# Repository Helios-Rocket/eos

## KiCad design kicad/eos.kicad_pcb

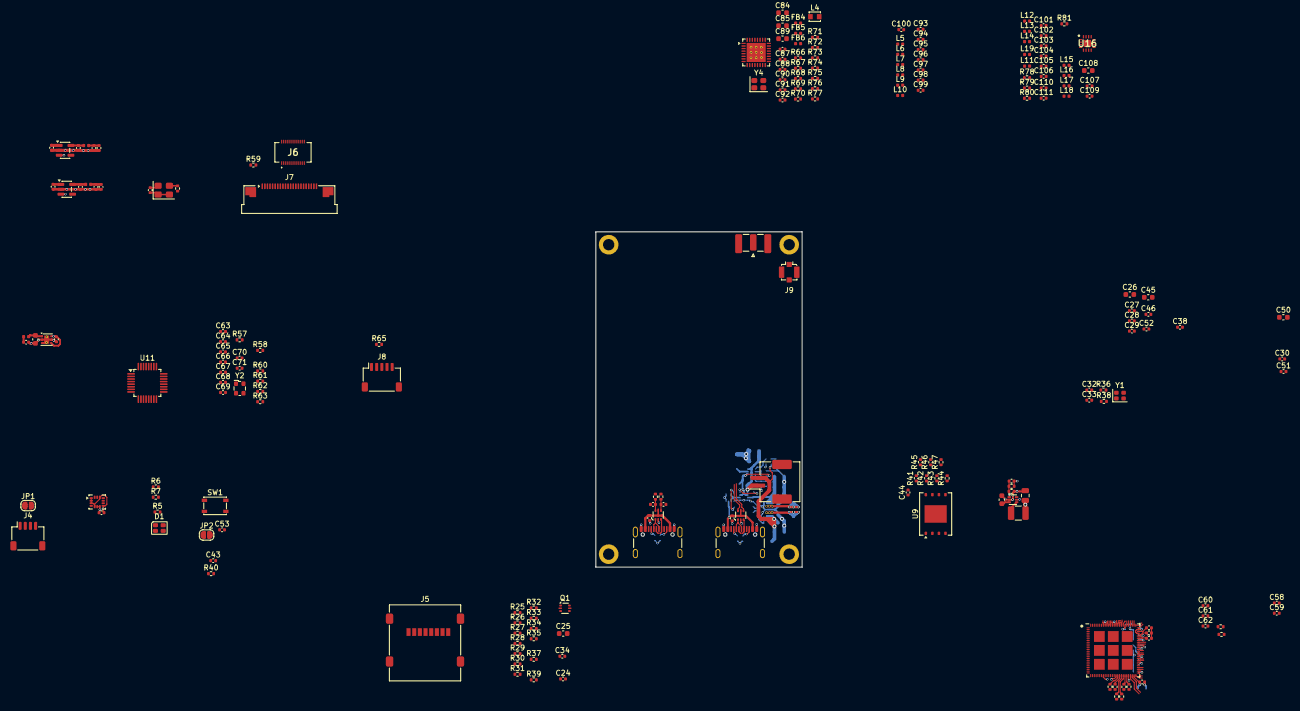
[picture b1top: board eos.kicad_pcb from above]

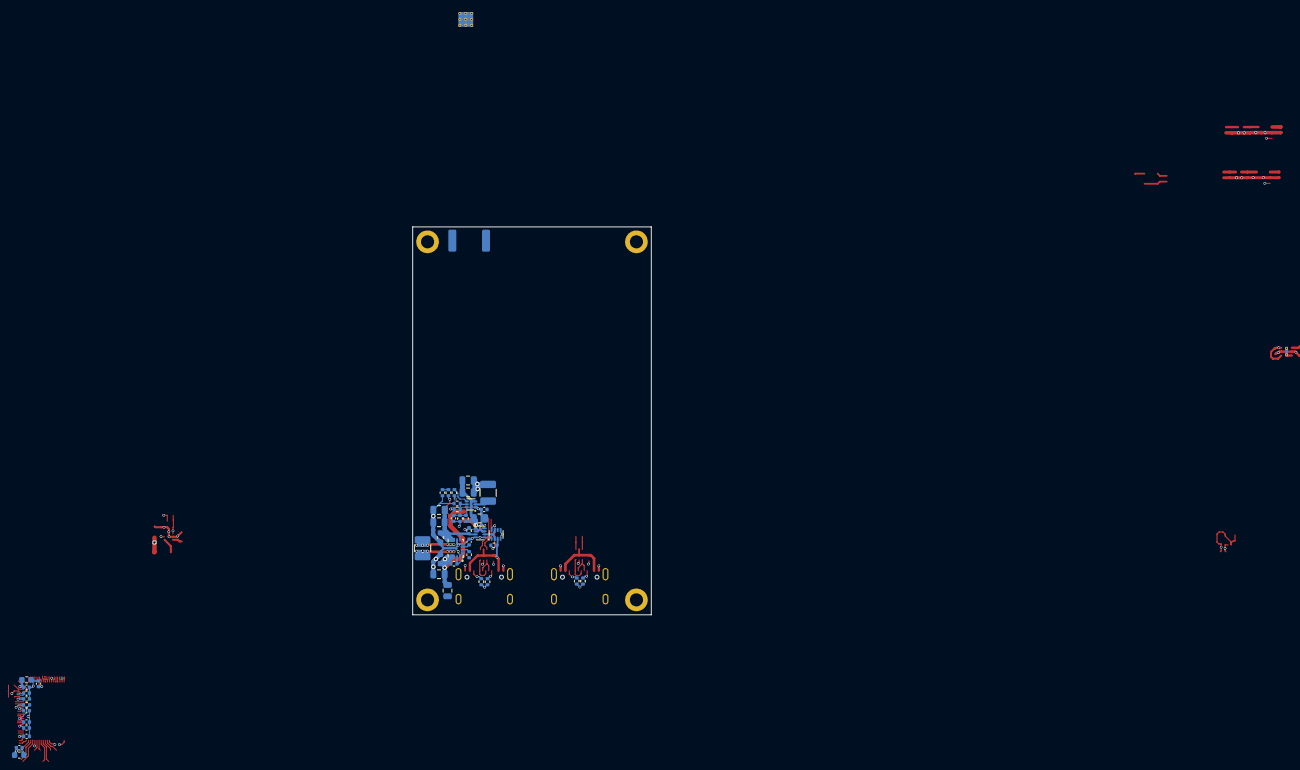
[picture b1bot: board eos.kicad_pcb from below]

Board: 4 copper layers, 40.0 x 65.0 mm, 251 parts (45 on the bottom side), 196 nets.

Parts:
C1, C11, C39, C40, C41, C42, C43, C47, C58, C60, C67, C68, C69, C72, C73, C75, C76, C78, C81, C83, C86, C87: 1u; C_0402_1005Metric
C2, C5, C25, C26, C35, C45, C50, C82: 10u; C_0603_1608Metric
C3, C4: 10u; C_0805_2012Metric
C6, C7, C17, C18, C19, C23: 22u; C_0805_2012Metric
C9, C14, C20, C24, C27, C28, C29, C30, C31, C36, C37, C38, C44, C46, C48, C49, C51, C52, C54, C57, C59, C62, C63, C64, C65, C66, C70, C71, C74, C77, C79, C88: 0.1u; C_0402_1005Metric
C12, C13, C34, C110: TBD; C_0402_1005Metric
C15: 10p; C_0402_1005Metric
C21, C95: 22p; C_0402_1005Metric
C22, C55, C89: 4.7u; C_0603_1608Metric
C32, C33: 16p; C_0402_1005Metric
C53, C56, C61, C80, C91: 10n; C_0402_1005Metric
C84, C85, C108: 2.2u; C_0603_1608Metric
C90: 1n; C_0402_1005Metric
C92: 2200p; C_0402_1005Metric
C93: 2.2p; C_0402_1005Metric
C94, C111: 18p; C_0402_1005Metric
C96, C97: 1.8p; C_0402_1005Metric
C98: 3.9p; C_0402_1005Metric
C99: 7.5p; C_0402_1005Metric
C100, C106: 47p; C_0402_1005Metric
C101: 6.8p; C_0402_1005Metric
C102: 1.1p; C_0402_1005Metric
C103: 2.0p; C_0402_1005Metric
C104: 1.2p; C_0402_1005Metric
C105: 2.7p; C_0402_1005Metric
C107, C109: 100p; C_0402_1005Metric
D1: LED_RGBA; LED_Cree-PLCC4_2x2mm_CW
FB1, FB2, FB3, FB4, FB5, FB6: BLM15BB470SN1D; L_0402_1005Metric
H1, H2, H3, H4: MountingHole_Pad; MountingHole_2.2mm_M2_DIN965_Pad
J1: Debug; USB_C_Receptacle_GCT_USB4105-xx-A_16P_TopMnt_Horizontal
J2: Video; USB_C_Receptacle_GCT_USB4105-xx-A_16P_TopMnt_Horizontal
J3: Power In; JST_ZE_SM02B-ZESS-TB_1x02-1MP_P1.50mm_Horizontal
J4: Comms; JST_SH_SM04B-SRSS-TB_1x04-1MP_P1.00mm_Horizontal
J5: Micro_SD_Card; microSD_HC_Molex_47219-2001
J6: Sensor; DF30FC24DS04V81
J7: COTS; Amphenol_F32Q-1A7x1-11022_1x22-1MP_P0.5mm_Horizontal
J8: Split 4; JST_SH_SM05B-SRSS-TB_1x05-1MP_P1.00mm_Horizontal
J9: 915M; U.FL_Molex_MCRF_73412-0110_Vertical
J10: 2.4G; SMA_Samtec_SMA-J-P-H-ST-EM1_EdgeMount
JP1: SolderJumper_2_Open; SolderJumper-2_P1.3mm_Open_RoundedPad1.0x1.5mm
JP2: Boot; SolderJumper-2_P1.3mm_Open_RoundedPad1.0x1.5mm
L1: 1.5u; L_1210_3225Metric
L2: 3.3u; L_1210_3225Metric
L3: 2.2u; L_1210_3225Metric
L4: 2.2u; L_Murata_LQH2MCNxxxx02_2.0x1.6mm
L5: 24n; L_0402_1005Metric
L6: 7.5n; L_0402_1005Metric
L7: 3.9n; L_0402_1005Metric
L8: 4.7n; L_0402_1005Metric
L9: 22n; L_0402_1005Metric
L10: 12n; L_0402_1005Metric
L11, L17: 1.1n; L_0402_1005Metric
L12: 1.6n; L_0402_1005Metric
L13: 1.5n; L_0402_1005Metric
L14: 18n; L_0402_1005Metric
L15: 0.9nH; L_0402_1005Metric
L16: 2.7n; L_0402_1005Metric
L18: 1.4n; L_0402_1005Metric
L19: 2.4n; L_0402_1005Metric
Q1: Q_Dual_NMOS_PMOS_S1G1D2S2G2D1; SOT-666
R1, R4, R12, R13: 5.1k; R_0402_1005Metric
R2, R10, R11, R19, R20, R25, R40, R41, R48, R60, R63, R65: 10k; R_0402_1005Metric
R3, R22: 100k; R_0402_1005Metric
R5, R6, R7: 330R; R_0402_1005Metric
R14, R15: 22R; R_0402_1005Metric
R16: 76.8k; R_0402_1005Metric
R17: 45.3k; R_0402_1005Metric
R18: 30k; R_0402_1005Metric
R21: 340k; R_0402_1005Metric
R23, R24: 499k; R_0402_1005Metric
R26, R27, R28, R29, R30, R31: 51k; R_0402_1005Metric
R32, R33, R34, R35, R36, R37, R38, R39, R42, R43, R44, R45, R46, R47, R49, R50, R51, R52, R53, R54, R64, R78: 0R; R_0402_1005Metric
R55, R56: 4.02k; R_0402_1005Metric
R57, R58: 37R4; R_0402_1005Metric
R59: 1k; R_0402_1005Metric
R61, R62: 2.2k; R_0402_1005Metric
R66, R69, R70, R71, R76, R77: 470R; R_0402_1005Metric
R67, R68, R72, R73, R74, R75: 220R; R_0402_1005Metric
R79, R80: TBD; R_0402_1005Metric
R81: 2k; R_0402_1005Metric
SW1: Reset; SW_SPST_PTS810
U1: TPS63071; VREG_TPS630701RNMR
U2, U5: USBLC6-2P6; SOT-666
U3, U4: LM66200; SOT-583-8
U6: TPS56425x; SOT-563
U7: LSM6DSV32X; LGA-14_3x2.5mm_P0.5mm_LayoutBorder3x4y
U8: TLV62569DRL; SOT-563
U9: GD25Q256EY; WSON-8-1EP_8x6mm_P1.27mm_EP3.4x4.3mm
U10: ESP32-P4
U11: TVP5150AM1; TQFP-32_5x5mm_P0.5mm
U12: TLV73328PDBV; SOT-23-5
U13: TLV73315PDBV; SOT-23-5
U14: TPS7A26; WSON-6-1EP_2x2mm_P0.65mm_EP1x1.6mm_ThermalVias
U15: LR2021; QFN-32-1EP_5x5mm_P0.5mm_EP3.7x3.7mm_ThermalVias
U16: SKY85329-11; QFN50P250X250X45-17N-D
Y1: 40MHz; Crystal_SMD_2016-4Pin_2.0x1.6mm
Y2: 14.31818MHz; Oscillator_SMD_ECS_2520MV-xxx-xx-4Pin_2.5x2.0mm
Y3: ECS-TXO-32CSMV; Crystal_SMD_3225-4Pin_3.2x2.5mm
Y4: ATX-12-F; Crystal_SMD_2520-4Pin_2.5x2.0mm

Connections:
5V_PG: R3.2, U1.2 (PG), U10.1 (GPIO1)
+1V5: C78.1, C79.1, FB2.2, J6.20
+1V8: C66.1, C82.1, FB3.1, U11.20 (DVDD), U14.1 (OUT)
+2V8: C73.1, C80.1, FB1.1, J6.19, U12.5 (OUT), Y3.4 (VDD)
+3.3V: C15.1, C18.1, C19.1, C20.1, C22.1, C26.1, C27.1, C28.1, C29.1, C35.1, C36.1, C38.1, C45.1, C46.1, C49.1, C52.1, C55.1, C56.1, C57.1, C65.1, C72.1, C76.1, C81.1, D1.4 (A), FB6.2, J7.22, JP1.2 (B), L2.2, Q1.4 (S), R17.1, R19.1, R40.1, R48.2, R60.1, R61.1, R62.1, R63.1, U7.1 (SDO/SA0), U7.2 (SDX), U7.3 (SCX), U7.5 (VDDIO), U7.8 (VDD), U7.12 (CS), U8.3 (VIN), U10.9 (VDD_LP), U10.21 (VDD_IO_0), U10.51 (VDD_USBPHY), U10.62 (VDD_IO_4), U10.75 (VDD_LDO), U10.77 (VDD_DCDCC), U10.96 (VDD_IO_6), U10.101 (VDD_ANA), U10.102 (VDD_BAT), U11.10 (IO_DVDD), U12.1 (IN), U13.1 (IN), U14.4 (EN), U14.6 (IN)
+5V: C14.1, C17.1, C107.2, C108.2, J8.1, L15.1, R16.1, U3.2 (VOUT), U3.7 (VOUT), U6.1 (VIN), U16.16 (VCC1)
+5VP: C2.1, C6.1, C7.1, R3.1, R10.1, U1.5 (FB), U1.7 (VOUT), U3.3 (VIN1)
+BATT: C3.1, C4.1, C5.1, J3.2, R2.1, R21.1, U1.12 (VIN)
/cameras/+2V8F: C74.1, C75.1, FB1.2, J6.18
/cameras/MCLK: J6.14, R64.2
/cameras/NTSC_IN: J8.2, R57.1
/eos/3.3PG: R19.2, U6.4 (PG)
/mcu/BOOT_MODE: JP2.2 (B), U10.66 (GPIO35)
/mcu/EN_DCDC: U8.5 (EN), U10.79 (EN_DCDC)
/mcu/FB_DCDC: C21.2, R23.2, R24.1, U8.1 (FB), U10.78 (FB_DCDC)
/mcu/FLASH_CLK: R43.2, U10.32 (FLASH_CK)
/mcu/FLASH_DI: R44.2, U10.33 (FLASH_D)
/mcu/FLASH_DO: R45.2, U10.28 (FLASH_Q)
/mcu/FLASH_HOLD: R47.2, U10.31 (FLASH_HOLD)
/mcu/FLASH_~CS: R42.2, U10.27 (FLASH_CS)
/mcu/FLASH_~WP: R46.2, U10.29 (FLASH_WP)
/mcu/SD_CLK: C34.1, R29.2, R35.2, U10.84 (GPIO43)
/mcu/SD_CMD: R28.2, R34.2, U10.86 (GPIO44)
/mcu/SD_D0: R30.2, R37.2, U10.80 (GPIO39)
/mcu/SD_D1: R31.2, R39.2, U10.81 (GPIO40)
/mcu/SD_D2: R26.2, R32.2, U10.82 (GPIO41)
/mcu/SD_D3: R27.2, R33.2, U10.83 (GPIO42)
/mcu/SD_RST: Q1.5 (G), R25.1, U10.5 (GPIO5)
/mcu/~ESP_EN: C43.1, C53.1, R40.2, SW1.2, U10.103 (CHIP_PU)
/radio/RX_EN: R67.2, U16.1 (RXEN)
/radio/TX_EN: R68.2, U16.2 (TXEN)
/radio/VR_PA: C90.1, C100.1, C106.1, L10.2, L14.2, U15.1 (VR_PA)
BATT_ADC: R21.2, R22.1, U10.98 (ADC2_CHANNEL5)
CSI_CLK+: J6.8, J7.9, R51.2
CSI_CLK-: J6.7, J7.8, R52.2
CSI_D0+: J6.9, J7.3, R50.2
CSI_D0-: J6.10, J7.2, R49.2
CSI_D1+: J6.5, J7.6, R54.2
CSI_D1-: J6.6, J7.5, R53.2
EXT_SCL: J4.4, U10.56 (GPIO27/USB1P1_P1)
EXT_SDA: J4.3, U10.55 (GPIO26/USB1P1_N1)
FID: U10.2 (GPIO2), U11.23 (FID)
GND: C1.2, C2.2, C3.2, C4.2, C5.2, C6.2, C7.2, C9.2, C11.2, C12.1, C13.2, C14.2, C17.2, C18.2, C19.2, C20.2, C22.2, C23.2, C24.2, C25.2, C26.2, C27.2, C28.2, C29.2, C30.2, C31.2, C32.1, C33.1, C34.2, C35.2, C36.2, C37.2, C38.2, C39.2, C40.2, C41.2, C42.2, C43.2, C44.2, C45.2, C46.2, C47.2, C48.2, C49.2, C50.2, C51.2, C52.2, C53.2, C54.2, C55.2, C56.2, C57.2, C58.2, C59.2, C60.2, C61.2, C62.2, C63.2, C64.2, C65.2, C66.2, C68.2, C69.2, C71.2, C72.2, C73.2, C74.2, C75.2, C76.2, C77.2, C78.2, C79.2, C80.2, C81.2, C82.2, C83.2, C84.2, C85.2, C86.2, C87.2, C88.2, C89.2, C90.2, C91.2, C93.2, C97.2, C98.2, C99.2, C100.2, C103.2, C104.2, C105.2, C106.2, C107.1, C108.1, C110.2, H1.1 (1_1), H2.1 (1_1), H3.1 (1_1), H4.1 (1_1), J1.A1 (GND), J1.A12 (GND), J1.B1 (GND), J1.B12 (GND), J2.A1 (GND), J2.A12 (GND), J2.B1 (GND), J2.B12 (GND), J3.1, J4.1, J5.6 (VSS), J6.13, J6.15, J6.17, J7.1, J7.4, J7.7, J7.10, J7.13, J7.16, J7.19, J9.2 (Ext), J10.2 (Ext), JP2.1 (A), L9.2, L17.1, Q1.1 (S), R1.2, R4.2, R12.2, R13.2, R18.2, R20.2, R22.2, R24.2, R25.2, R55.2, R56.2, R58.1, R59.1, R65.2, R79.2, R80.2, R81.2, SW1.1, U1.4 (GND), U1.6 (FB2), U1.10 (GND), U1.15 (VSEL), U2.2 (GND), U3.1 (GND), U3.4 (~ON), U3.5 (GND), U4.1 (GND), U4.4 (~ON), U4.5 (GND), U5.2 (GND), U6.3 (GND), U7.6 (GND), U7.7 (GND), U8.2 (GND), U9.4 (VSS), U9.9 (PAD), U10.105 (GND), U11.3 (PLL_AGND), U11.7 (AGND), U11.19 (DGND), U11.31 (CH_AGND), U12.2 (GND), U13.2 (GND), U14.2 (GND), U14.3 (PG), U14.5 (GND), U14.7 (GND), U15.15 (GND_DCC), U15.30 (GND), U15.33 (GND), U16.6 (GND), U16.9 (GND), U16.11 (GND), U16.13 (GND), U16.15 (GND), U16.17 (GND), Y1.2 (G), Y1.4 (G), Y2.2 (GND), Y3.1 (GND), Y3.2 (GND), Y4.1 (GND), Y4.2 (GND)
HSYNC: U10.4 (GPIO4), U11.25 (HSYNC)
IMU_INT1: U7.4 (INT1), U10.22 (GPIO20/ADC1_CHANNEL4)
IO0_PowerEN: J7.17, U10.63 (GPIO32), U12.3 (EN), U13.3 (EN)
LED_BLUE: R7.2, U10.20 (GPIO19/ADC1_CHANNEL3)
LED_GREEN: R6.2, U10.19 (GPIO18/ADC1_CHANNEL2)
LED_RED: R5.2, U10.18 (GPIO17/ADC1_CHANNEL1)
LR_BUSY: R76.2, U10.6 (GPIO6)
LR_IRQ1: R66.2, U10.13 (GPIO12)
LR_IRQ2: R69.2, U10.14 (GPIO13)
LR_IRQ3: R70.2, U10.15 (GPIO14)
LR_IRQ4: R71.2, U10.16 (GPIO15)
LR_MISO: R72.2, U10.11 (GPIO10)
LR_MOSI: R73.2, U10.8 (GPIO8)
LR_SCK: R74.2, U10.10 (GPIO9)
LR_~CS: R75.2, U10.7 (GPIO7)
LR_~RESET: R77.2, U10.12 (GPIO11)
MIPI_I2C_SCL: J6.11, J7.20, U10.61 (GPIO31)
MIPI_I2C_SDA: J6.12, J7.21, U10.60 (GPIO30)
unnamed: C12.2, R14.1, U5.6 (I/O1)
unnamed: C13.1, R15.1, U5.4 (I/O2)
unnamed: C32.2, R36.1, Y1.3
unnamed: C33.2, R38.1, Y1.1
unnamed: C70.1, R57.2, R58.2
unnamed: C93.1, C94.2, L5.1
unnamed: C95.1, C96.1, C99.1, L7.2
unnamed: C95.2, L8.1
unnamed: C96.2, C98.1, L6.2, L7.1
unnamed: C101.1, C102.1, C105.1, L12.2
unnamed: C101.2, L13.1
unnamed: C102.2, C104.1, L11.2, L12.1
unnamed: C103.1, L11.1, R78.2, R80.1
unnamed: C109.1, L17.2
unnamed: C110.1, C111.2, L19.1
unnamed: D1.3 (BK), R7.1
unnamed: D1.2 (GK), R6.1
unnamed: D1.1 (RK), R5.1
unnamed: J1.A5 (CC1), R1.1
unnamed: J1.B5 (CC2), R4.1
unnamed: J1.A6 (D+), J1.B6 (D+), U2.3 (I/O2)
unnamed: J1.A7 (D-), J1.B7 (D-), U2.1 (I/O1)
unnamed: J2.A5 (CC1), R12.1
unnamed: J2.B5 (CC2), R13.1
unnamed: J2.A6 (D+), J2.B6 (D+), U5.3 (I/O2)
unnamed: J2.A7 (D-), J2.B7 (D-), U5.1 (I/O1)
unnamed: J4.2, JP1.1 (A)
unnamed: J5.5 (CLK), R35.1
unnamed: J5.3 (CMD), R34.1
unnamed: J5.7 (DAT0), R37.1
unnamed: J5.8 (DAT1), R39.1
unnamed: J5.1 (DAT2), R32.1
unnamed: J5.2 (DAT3/CD), R33.1
unnamed: C24.1, C25.1, J5.4 (VDD), Q1.3 (D)
unnamed: J6.24, R59.2
unnamed: J8.5, Q1.6 (D)
unnamed: C94.1, C97.1, J9.1 (In), L6.1, L9.1
unnamed: C109.2, J10.1 (In), L16.1
unnamed: L5.2, U15.27 (RFO_LF), U15.28 (RFO_LF)
unnamed: R2.2, U1.1 (PS/SYNC), U1.14 (EN)
unnamed: L1.1, U1.11 (L1)
unnamed: L1.2, U1.9 (L2)
unnamed: C9.1, U1.3 (VAUX)
unnamed: R11.2, U4.8 (ST)
unnamed: R16.2, R18.1, U6.5 (EN)
unnamed: C15.2, R17.2, R20.1, U6.6 (FB)
unnamed: L2.1, U6.2 (SW)
unnamed: L3.1, U8.4 (SW)
unnamed: R43.1, U9.6 (SCLK)
unnamed: R44.1, U9.5 (SI/IO0)
unnamed: R45.1, U9.2 (SO/IO1)
unnamed: R41.2, R42.1, U9.1 (~CS)
unnamed: R47.1, U9.7 (~HOLD/~RESET/IO3)
unnamed: R46.1, U9.3 (~WP/IO2)
unnamed: R52.1, U10.45 (CSI_CLKN)
unnamed: R51.1, U10.44 (CSI_CLKP)
unnamed: R49.1, U10.42 (CSI_DATAN0)
unnamed: R53.1, U10.46 (CSI_DATAN1)
unnamed: R50.1, U10.43 (CSI_DATAP0)
unnamed: R54.1, U10.47 (CSI_DATAP1)
unnamed: R56.1, U10.48 (CSI_REXT)
unnamed: R55.1, U10.34 (DSI_REXT)
unnamed: R48.1, U10.68 (GPIO36)
unnamed: R36.2, U10.99 (XTAL_N)
unnamed: R38.2, U10.100 (XTAL_P)
unnamed: C70.2, U11.1 (AIP1A)
unnamed: C71.1, U11.2 (AIP1B)
unnamed: C67.2, C69.1, U11.30 (REFM)
unnamed: C67.1, C68.1, U11.29 (REFP)
unnamed: U11.5 (OSC), Y2.3 (OUT)
unnamed: R63.2, U11.28 (~PDN)
unnamed: C77.1, FB2.1, U13.5 (OUT)
unnamed: R76.1, U15.25 (BUSY)
unnamed: R71.1, U15.18 (DIO6)
unnamed: R70.1, U15.11 (DIO7)
unnamed: R69.1, U15.10 (DIO8)
unnamed: R68.1, U15.9 (DIO9)
unnamed: R67.1, U15.8 (DIO10)
unnamed: R66.1, U15.7 (DIO11)
unnamed: L4.2, U15.16 (LXA)
unnamed: L4.1, U15.14 (LXB)
unnamed: R72.1, U15.21 (MISO)
unnamed: R73.1, U15.22 (MOSI)
unnamed: L19.2, U15.32 (RFI_HF)
unnamed: L8.2, L10.1, U15.29 (RFI_LF)
unnamed: L13.2, L14.1, U15.31 (RFO_HF)
unnamed: R74.1, U15.23 (SCK)
unnamed: C88.1, C89.1, FB6.1, U15.17 (VBAT)
unnamed: C86.1, FB5.1, U15.12 (VDCC1)
unnamed: C87.1, FB5.2, U15.26 (VDCC2)
unnamed: C84.1, FB4.1, U15.13 (VPAX1)
unnamed: C85.1, FB4.2, U15.2 (VPAX2)
unnamed: C91.1, U15.6 (VTCXO/VNTC), Y4.4 (VDD)
unnamed: C92.2, U15.4 (XTA)
unnamed: R77.1, U15.20 (~NRESET)
unnamed: R75.1, U15.24 (~NSS)
unnamed: L16.2, U16.10 (ANT)
unnamed: L18.1, U16.7 (LNAIN)
unnamed: C111.1, U16.5 (RX)
unnamed: L18.2, U16.8 (SWRX)
unnamed: R78.1, R79.1, U16.3 (TX)
unnamed: L15.2, U16.14 (VCC2)
unnamed: R64.1, Y3.3 (OUT)
unnamed: C92.1, Y4.3 (OUT)
ONBOARD_SCL: R62.2, U7.13 (SCL), U10.24 (GPIO22/ADC1_CHANNEL6), U11.22 (SCL)
ONBOARD_SDA: R61.2, U7.14 (SDA), U10.23 (GPIO21/ADC1_CHANNEL5), U11.21 (SDA)
ON_BATT: R10.2, U3.8 (ST), U10.104 (GPIO0)
P_DET: R81.1, U10.17 (GPIO16/ADC1_CHANNEL0), U16.4 (DET)
SCLK: U10.87 (GPIO45), U11.9 (SCLK)
SPLIT4_EN: Q1.2 (G), R65.1, U10.64 (GPIO33)
SPLIT4_RX: J8.4, U10.70 (GPIO38)
SPLIT4_TX: J8.3, U10.69 (GPIO37)
USB_DEBUG+: U2.4 (I/O2), U10.53 (USB1P1_P0)
USB_DEBUG-: U2.6 (I/O1), U10.52 (USB1P1_N0)
USB_HS+: R15.2, U10.50 (USB-DP)
USB_HS-: R14.2, U10.49 (USB-DM)
VDD: C21.1, C23.1, C30.1, C37.1, C50.1, C51.1, C54.1, L3.2, R23.1, U10.26 (VDD_HP_0), U10.54 (VDD_HP_1), U10.76 (VDD_HP_2), U10.91 (VDD_HP_3)
VDDA: C63.1, C64.1, C83.1, FB3.2, U11.4 (PLL_AVDD), U11.32 (CH_AVDD), Y2.4 (VDD)
VFLASH: C42.1, C44.1, C58.1, C59.1, R41.1, U9.8 (VCC), U10.30 (VDD_FLASH_IO), U10.71 (VDDO_FLASH)
VMIPI: C40.1, C60.1, C61.1, C62.1, U10.41 (VDD_MIPI_DPHY), U10.73 (VDDO_3)
VPSRAM: C41.1, C47.1, C48.1, U10.59 (VDD_PSRAM_0), U10.67 (VDD_PSRAM_1), U10.72 (VDDO_PSRAM)
VSYNC: U10.3 (GPIO3), U11.24 (VSYNC)
VUSB: U3.6 (VIN2), U4.2 (VOUT), U4.7 (VOUT)
VUSB1: C1.1, J1.A4 (VBUS), J1.A9 (VBUS), J1.B4 (VBUS), J1.B9 (VBUS), R11.1, U2.5 (VBUS), U4.3 (VIN1)
VUSB2: C11.1, J2.A4 (VBUS), J2.A9 (VBUS), J2.B4 (VBUS), J2.B9 (VBUS), U4.6 (VIN2), U5.5 (VBUS)
V_SD: C31.1, C39.1, R26.1, R27.1, R28.1, R29.1, R30.1, R31.1, U10.74 (VDDO_4), U10.85 (VDD_IO_5)
Y0: U10.88 (GPIO46), U11.18 (YOUT0)
Y1: U10.89 (GPIO47), U11.17 (YOUT1)
Y2: U10.90 (GPIO48), U11.16 (YOUT2)
Y3: U10.92 (GPIO49/ADC2_CHANNEL0), U11.15 (YOUT3)
Y4: U10.93 (GPIO50/ADC2_CHANNEL1), U11.14 (YOUT4)
Y5: U10.94 (GPIO51/ADC2_CHANNEL2), U11.13 (YOUT5)
Y6: U10.95 (GPIO52/ADC2_CHANNEL3), U11.12 (YOUT6)
Y7: R60.2, U10.97 (GPIO53/ADC2_CHANNEL4), U11.11 (YOUT7/I2CSEL)
~TVP_RESET: U10.25 (GPIO23/ADC1_CHANNEL7), U11.8 (~RESETB)
